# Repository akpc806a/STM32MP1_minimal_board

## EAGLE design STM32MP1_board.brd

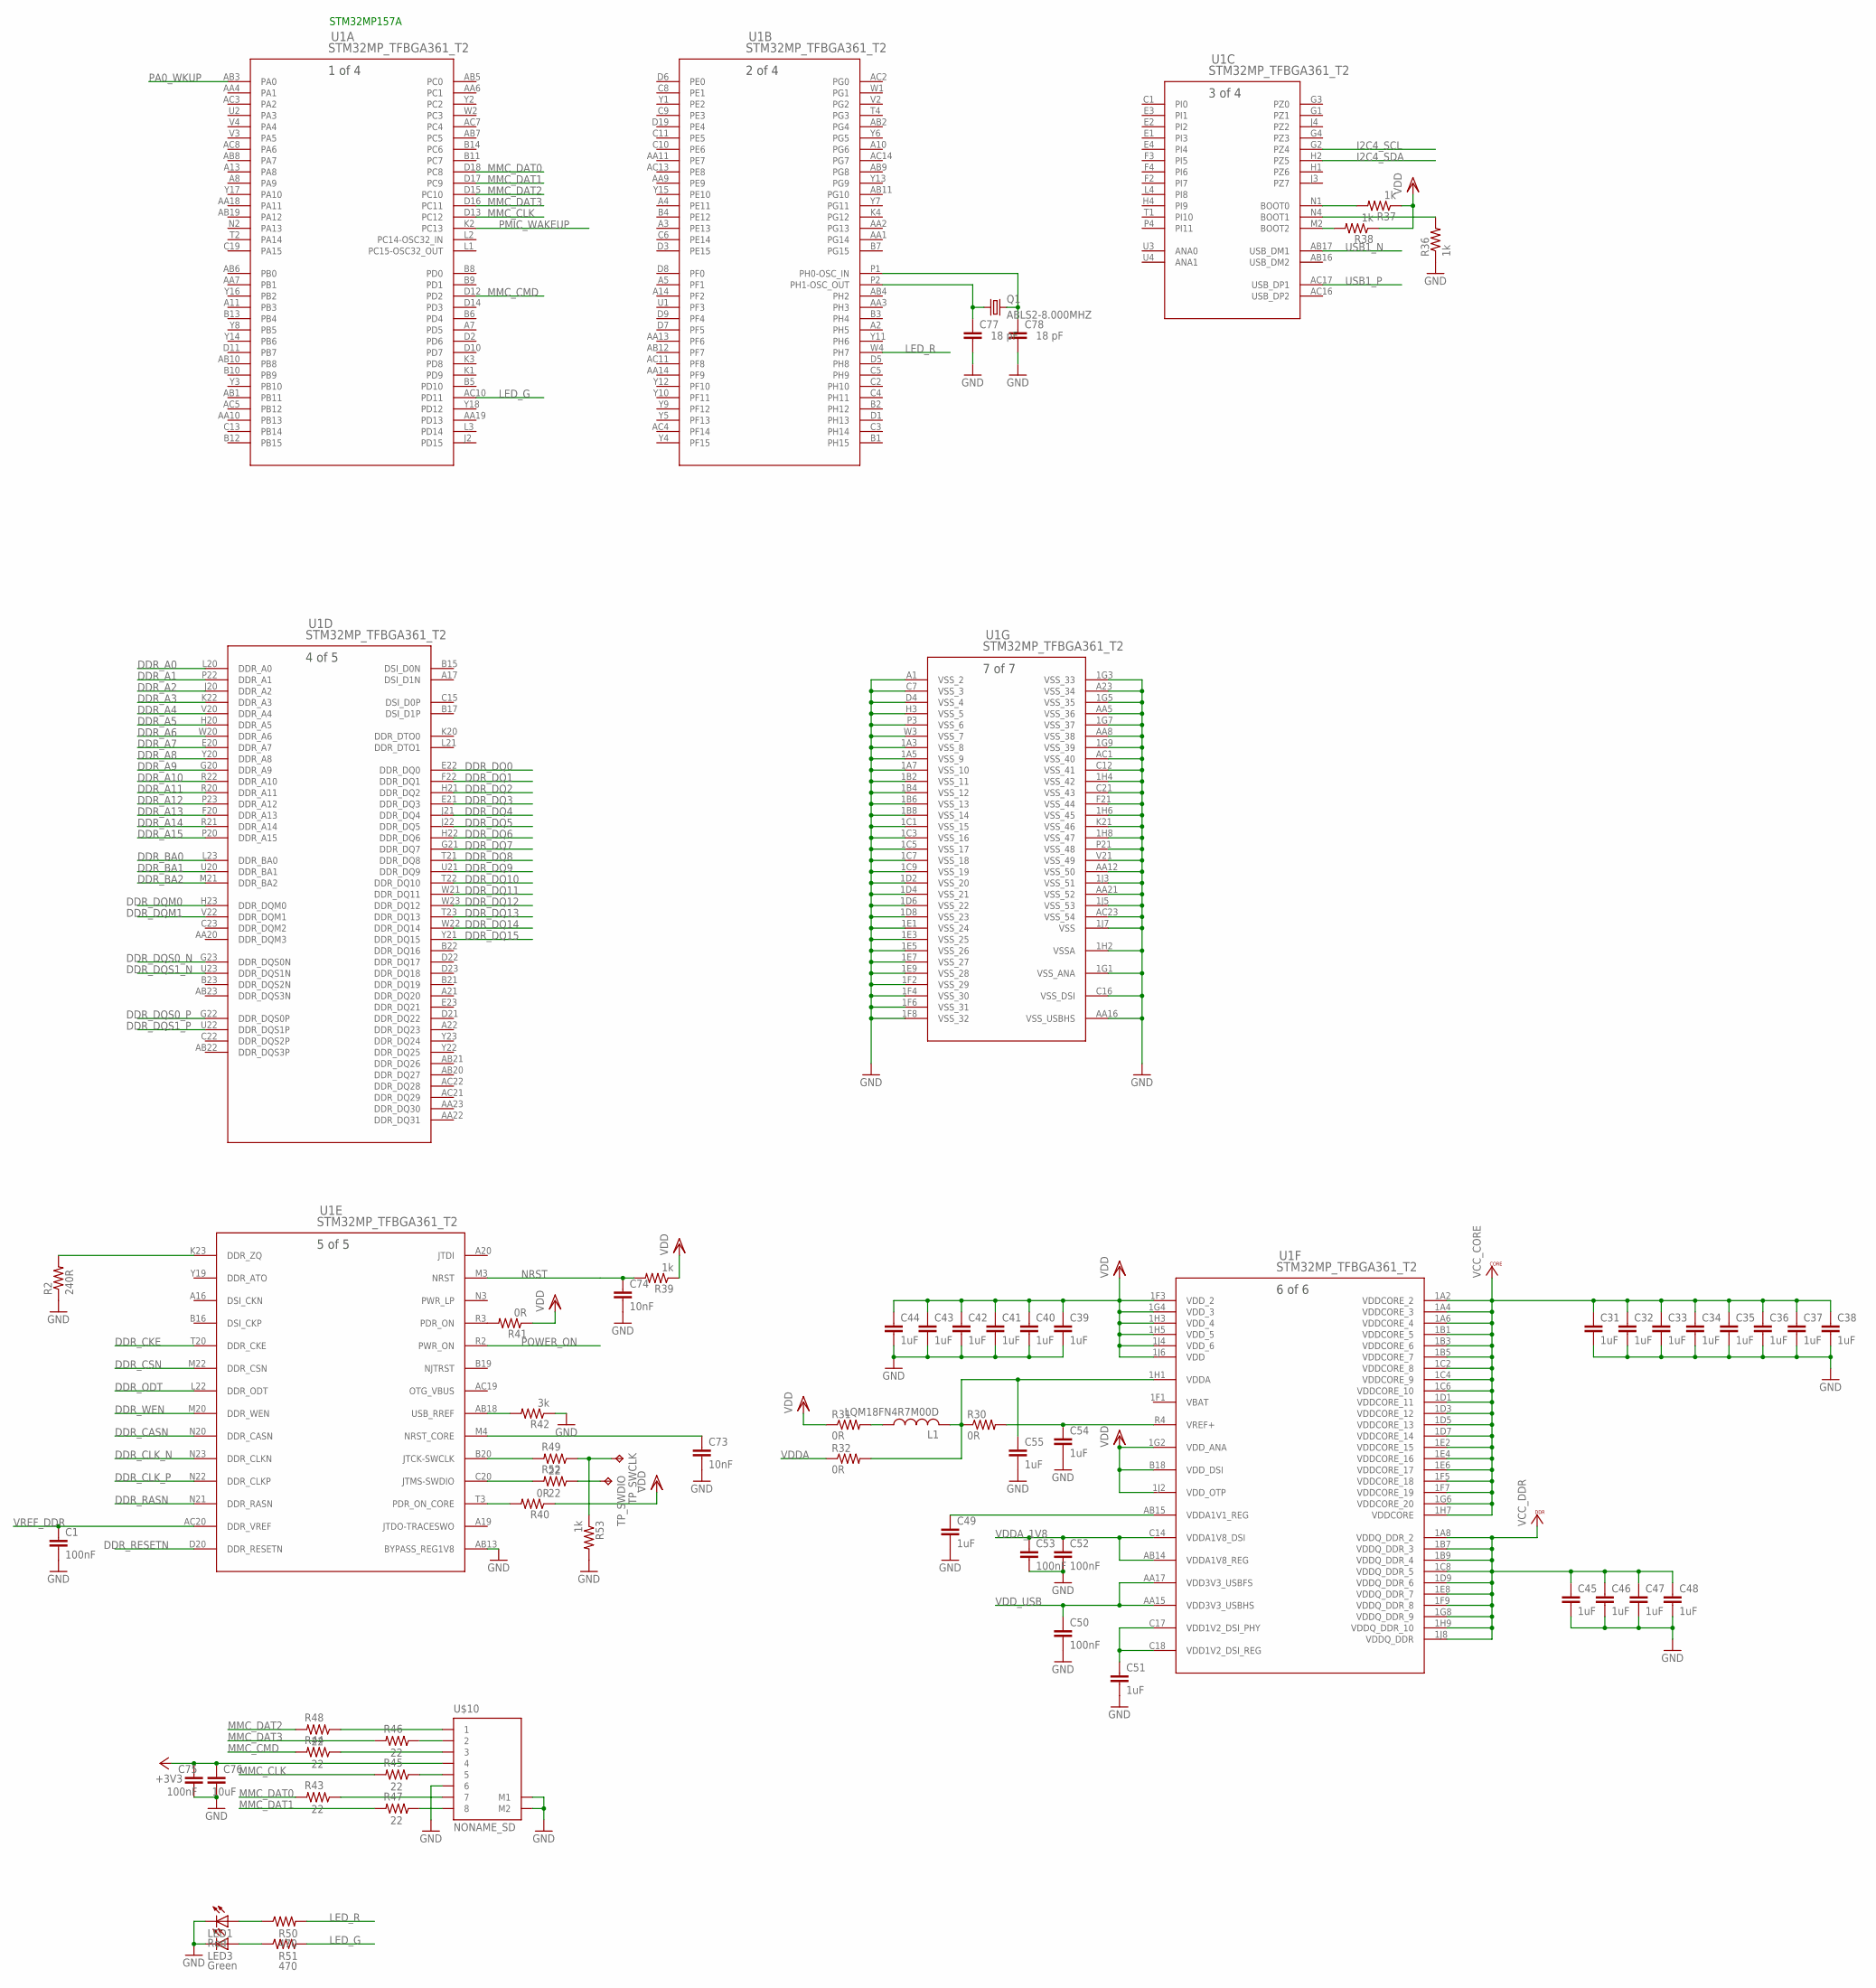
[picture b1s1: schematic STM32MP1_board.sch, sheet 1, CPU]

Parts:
C1, C50, C52, C53, C75: 100nF; C0402K
C31, C32, C33, C34, C35, C36, C37, C38, C39, C40, C41, C42, C43, C44, C45, C46, C47, C48, C49, C51, C54, C55: 1uF; C0402K
C73, C74: 10nF; C0402K
C76: 10uF; C0603K
C77, C78: 18 pF; C0603
L1: LQM18FN4R7M00D; R0603
LED1: Red; LED_SML0603
LED3: Green; LED_SML0603
Q1: ABLS2-8.000MHZ; SM49
R2: 240R; R0402
R30, R31, R32, R40, R41: 0R; R0402
R36, R37, R38, R39, R53: 1k; R0402
R42: 3k; R0402
R43, R44, R45, R46, R47, R48, R49, R52: 22; R0402
R50, R51: 470; R0402
TP_SWCLK: TPTP10SQ; TP10SQ
TP_SWDIO: TPTP10SQ; TP10SQ
U1: STM32MP_TFBGA361_T2; TFBGA361_12X12
U$10: NONAME_SD

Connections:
+3V3: C75.1, C76.1, U$10.4; also elsewhere on the board
DDR_A0: U1.L20 (DDR_A0); also elsewhere on the board
DDR_A1: U1.P22 (DDR_A1); also elsewhere on the board
DDR_A2: U1.J20 (DDR_A2); also elsewhere on the board
DDR_A3: U1.K22 (DDR_A3); also elsewhere on the board
DDR_A4: U1.V20 (DDR_A4); also elsewhere on the board
DDR_A5: U1.H20 (DDR_A5); also elsewhere on the board
DDR_A6: U1.W20 (DDR_A6); also elsewhere on the board
DDR_A7: U1.E20 (DDR_A7); also elsewhere on the board
DDR_A8: U1.Y20 (DDR_A8); also elsewhere on the board
DDR_A9: U1.G20 (DDR_A9); also elsewhere on the board
DDR_A10: U1.R22 (DDR_A10); also elsewhere on the board
DDR_A11: U1.R20 (DDR_A11); also elsewhere on the board
DDR_A12: U1.P23 (DDR_A12); also elsewhere on the board
DDR_A13: U1.F20 (DDR_A13); also elsewhere on the board
DDR_A14: U1.R21 (DDR_A14); also elsewhere on the board
DDR_A15: U1.P20 (DDR_A15)
DDR_BA0: U1.L23 (DDR_BA0); also elsewhere on the board
DDR_BA1: U1.U20 (DDR_BA1); also elsewhere on the board
DDR_BA2: U1.M21 (DDR_BA2); also elsewhere on the board
DDR_CASN: U1.N20 (DDR_CASN); also elsewhere on the board
DDR_CKE: U1.T20 (DDR_CKE); also elsewhere on the board
DDR_CLK_N: U1.N23 (DDR_CLKN); also elsewhere on the board
DDR_CLK_P: U1.N22 (DDR_CLKP); also elsewhere on the board
DDR_CSN: U1.M22 (DDR_CSN); also elsewhere on the board
DDR_DQ0: U1.E22 (DDR_DQ0); also elsewhere on the board
DDR_DQ1: U1.F22 (DDR_DQ1); also elsewhere on the board
DDR_DQ2: U1.H21 (DDR_DQ2); also elsewhere on the board
DDR_DQ3: U1.E21 (DDR_DQ3); also elsewhere on the board
DDR_DQ4: U1.J21 (DDR_DQ4); also elsewhere on the board
DDR_DQ5: U1.J22 (DDR_DQ5); also elsewhere on the board
DDR_DQ6: U1.H22 (DDR_DQ6); also elsewhere on the board
DDR_DQ7: U1.G21 (DDR_DQ7); also elsewhere on the board
DDR_DQ8: U1.T21 (DDR_DQ8); also elsewhere on the board
DDR_DQ9: U1.U21 (DDR_DQ9); also elsewhere on the board
DDR_DQ10: U1.T22 (DDR_DQ10); also elsewhere on the board
DDR_DQ11: U1.W21 (DDR_DQ11); also elsewhere on the board
DDR_DQ12: U1.W23 (DDR_DQ12); also elsewhere on the board
DDR_DQ13: U1.T23 (DDR_DQ13); also elsewhere on the board
DDR_DQ14: U1.W22 (DDR_DQ14); also elsewhere on the board
DDR_DQ15: U1.Y21 (DDR_DQ15); also elsewhere on the board
DDR_DQM0: U1.H23 (DDR_DQM0); also elsewhere on the board
DDR_DQM1: U1.V22 (DDR_DQM1); also elsewhere on the board
DDR_DQS0_N: U1.G23 (DDR_DQS0N); also elsewhere on the board
DDR_DQS0_P: U1.G22 (DDR_DQS0P); also elsewhere on the board
DDR_DQS1_N: U1.U23 (DDR_DQS1N); also elsewhere on the board
DDR_DQS1_P: U1.U22 (DDR_DQS1P); also elsewhere on the board
DDR_ODT: U1.L22 (DDR_ODT); also elsewhere on the board
DDR_RASN: U1.N21 (DDR_RASN); also elsewhere on the board
DDR_RESETN: U1.D20 (DDR_RESETN); also elsewhere on the board
DDR_WEN: U1.M20 (DDR_WEN); also elsewhere on the board
GND: C1.2, C31.2, C32.2, C33.2, C34.2, C35.2, C36.2, C37.2, C38.2, C39.2, C40.2, C41.2, C42.2, C43.2, C44.2, C45.2, C46.2, C47.2, C48.2, C49.2, C50.2, C51.2, C52.2, C53.2, C54.2, C55.2, C73.2, C74.2, C75.2, C76.2, C77.2, C78.2, LED1.C, LED3.C, R2.1, R36.1, R42.1, R53.2, U1.1A3 (VSS_8), U1.1A5 (VSS_9), U1.1A7 (VSS_10), U1.1B2 (VSS_11), U1.1B4 (VSS_12), U1.1B6 (VSS_13), U1.1B8 (VSS_14), U1.1C1 (VSS_15), U1.1C3 (VSS_16), U1.1C5 (VSS_17), U1.1C7 (VSS_18), U1.1C9 (VSS_19), U1.1D2 (VSS_20), U1.1D4 (VSS_21), U1.1D6 (VSS_22), U1.1D8 (VSS_23), U1.1E1 (VSS_24), U1.1E3 (VSS_25), U1.1E5 (VSS_26), U1.1E7 (VSS_27), U1.1E9 (VSS_28), U1.1F2 (VSS_29), U1.1F4 (VSS_30), U1.1F6 (VSS_31), U1.1F8 (VSS_32), U1.1G1 (VSS_ANA), U1.1G3 (VSS_33), U1.1G5 (VSS_35), U1.1G7 (VSS_37), U1.1G9 (VSS_39), U1.1H2 (VSSA), U1.1H4 (VSS_42), U1.1H6 (VSS_45), U1.1H8 (VSS_47), U1.1J3 (VSS_51), U1.1J5 (VSS_53), U1.1J7 (VSS), U1.A1 (VSS_2), U1.A23 (VSS_34), U1.AA5 (VSS_36), U1.AA8 (VSS_38), U1.AA12 (VSS_50), U1.AA16 (VSS_USBHS), U1.AA21 (VSS_52), U1.AB13 (BYPASS_REG1V8), U1.AC1 (VSS_40), U1.AC23 (VSS_54), U1.C7 (VSS_3), U1.C12 (VSS_41), U1.C16 (VSS_DSI), U1.C21 (VSS_43), U1.D4 (VSS_4), U1.F21 (VSS_44), U1.H3 (VSS_5), U1.K21 (VSS_46), U1.P3 (VSS_6), U1.P21 (VSS_48), U1.V21 (VSS_49), U1.W3 (VSS_7), U$10.6, U$10.M1, U$10.M2; also elsewhere on the board
I2C4_SCL: U1.G2 (PZ4); also elsewhere on the board
I2C4_SDA: U1.H2 (PZ5); also elsewhere on the board
LED_G: R51.2, U1.AC10 (PD11)
LED_R: R50.2, U1.W4 (PH7)
MMC_CLK: R45.2, U1.D13 (PC12)
MMC_CMD: R44.2, U1.D12 (PD2)
MMC_DAT0: R43.2, U1.D18 (PC8)
MMC_DAT1: R47.2, U1.D17 (PC9)
MMC_DAT2: R48.2, U1.D15 (PC10)
MMC_DAT3: R46.2, U1.D16 (PC11)
unnamed: R2.2, U1.K23 (DDR_ZQ)
unnamed: C49.1, U1.AB15 (VDDA1V1_REG)
unnamed: C51.1, U1.C17 (VDD1V2_DSI_PHY), U1.C18 (VDD1V2_DSI_REG)
unnamed: C55.1, L1.2, R30.1, R32.2, U1.1H1 (VDDA)
unnamed: C54.1, R30.2, U1.R4 (VREF+)
unnamed: L1.1, R31.2
unnamed: C73.1, U1.M4 (NRST_CORE)
unnamed: R36.2, U1.N4 (BOOT1)
unnamed: R37.2, U1.N1 (BOOT0)
unnamed: R38.2, U1.M2 (BOOT2)
unnamed: C74.1, R39.2
unnamed: R40.2, U1.T3 (PDR_ON_CORE)
unnamed: R41.2, U1.R3 (PDR_ON)
unnamed: R42.2, U1.AB18 (USB_RREF)
unnamed: R49.2, U1.B20 (JTCK-SWCLK)
unnamed: R52.2, U1.C20 (JTMS-SWDIO)
unnamed: R48.1, U$10.1
unnamed: R46.1, U$10.2
unnamed: R44.1, U$10.3
unnamed: R45.1, U$10.5
unnamed: R43.1, U$10.7
unnamed: R47.1, U$10.8
unnamed: R49.1, R53.1, TP_SWCLK.TP
unnamed: R52.1, TP_SWDIO.TP
unnamed: C78.1, Q1.2, U1.P1 (PH0-OSC_IN)
unnamed: C77.1, Q1.1, U1.P2 (PH1-OSC_OUT)
unnamed: LED1.A, R50.1
unnamed: LED3.A, R51.1
NRST: U1.M3 (NRST); also elsewhere on the board
PA0_WKUP: U1.AB3 (PA0); also elsewhere on the board
PMIC_WAKEUP: U1.K2 (PC13); also elsewhere on the board
POWER_ON: U1.R2 (PWR_ON); also elsewhere on the board
USB1_N: U1.AB17 (USB_DM1)
USB1_P: U1.AC17 (USB_DP1)
VBAT: U1.1F1 (VBAT)
VCC_CORE: C31.1, C32.1, C33.1, C34.1, C35.1, C36.1, C37.1, C38.1, U1.1A2 (VDDCORE_2), U1.1A4 (VDDCORE_3), U1.1A6 (VDDCORE_4), U1.1B1 (VDDCORE_5), U1.1B3 (VDDCORE_6), U1.1B5 (VDDCORE_7), U1.1C2 (VDDCORE_8), U1.1C4 (VDDCORE_9), U1.1C6 (VDDCORE_10), U1.1D1 (VDDCORE_11), U1.1D3 (VDDCORE_12), U1.1D5 (VDDCORE_13), U1.1D7 (VDDCORE_14), U1.1E2 (VDDCORE_15), U1.1E4 (VDDCORE_16), U1.1E6 (VDDCORE_17), U1.1F5 (VDDCORE_18), U1.1F7 (VDDCORE_19), U1.1G6 (VDDCORE_20), U1.1H7 (VDDCORE); also elsewhere on the board
VCC_DDR: C45.1, C46.1, C47.1, C48.1, U1.1A8 (VDDQ_DDR_2), U1.1B7 (VDDQ_DDR_3), U1.1B9 (VDDQ_DDR_4), U1.1C8 (VDDQ_DDR_5), U1.1D9 (VDDQ_DDR_6), U1.1E8 (VDDQ_DDR_7), U1.1F9 (VDDQ_DDR_8), U1.1G8 (VDDQ_DDR_9), U1.1H9 (VDDQ_DDR_10), U1.1J8 (VDDQ_DDR); also elsewhere on the board
VDD: C39.1, C40.1, C41.1, C42.1, C43.1, C44.1, R31.1, R37.1, R38.1, R39.1, R40.1, R41.1, U1.1F3 (VDD_2), U1.1G2 (VDD_ANA), U1.1G4 (VDD_3), U1.1H3 (VDD_4), U1.1H5 (VDD_5), U1.1J2 (VDD_OTP), U1.1J4 (VDD_6), U1.1J6 (VDD), U1.B18 (VDD_DSI); also elsewhere on the board
VDDA: R32.1; also elsewhere on the board
VDDA_1V8: C52.1, C53.1, U1.AB14 (VDDA1V8_REG), U1.C14 (VDDA1V8_DSI)
VDD_USB: C50.1, U1.AA15 (VDD3V3_USBHS), U1.AA17 (VDD3V3_USBFS); also elsewhere on the board
VREF_DDR: C1.1, U1.AC20 (DDR_VREF); also elsewhere on the board

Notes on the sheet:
STM32MP157A

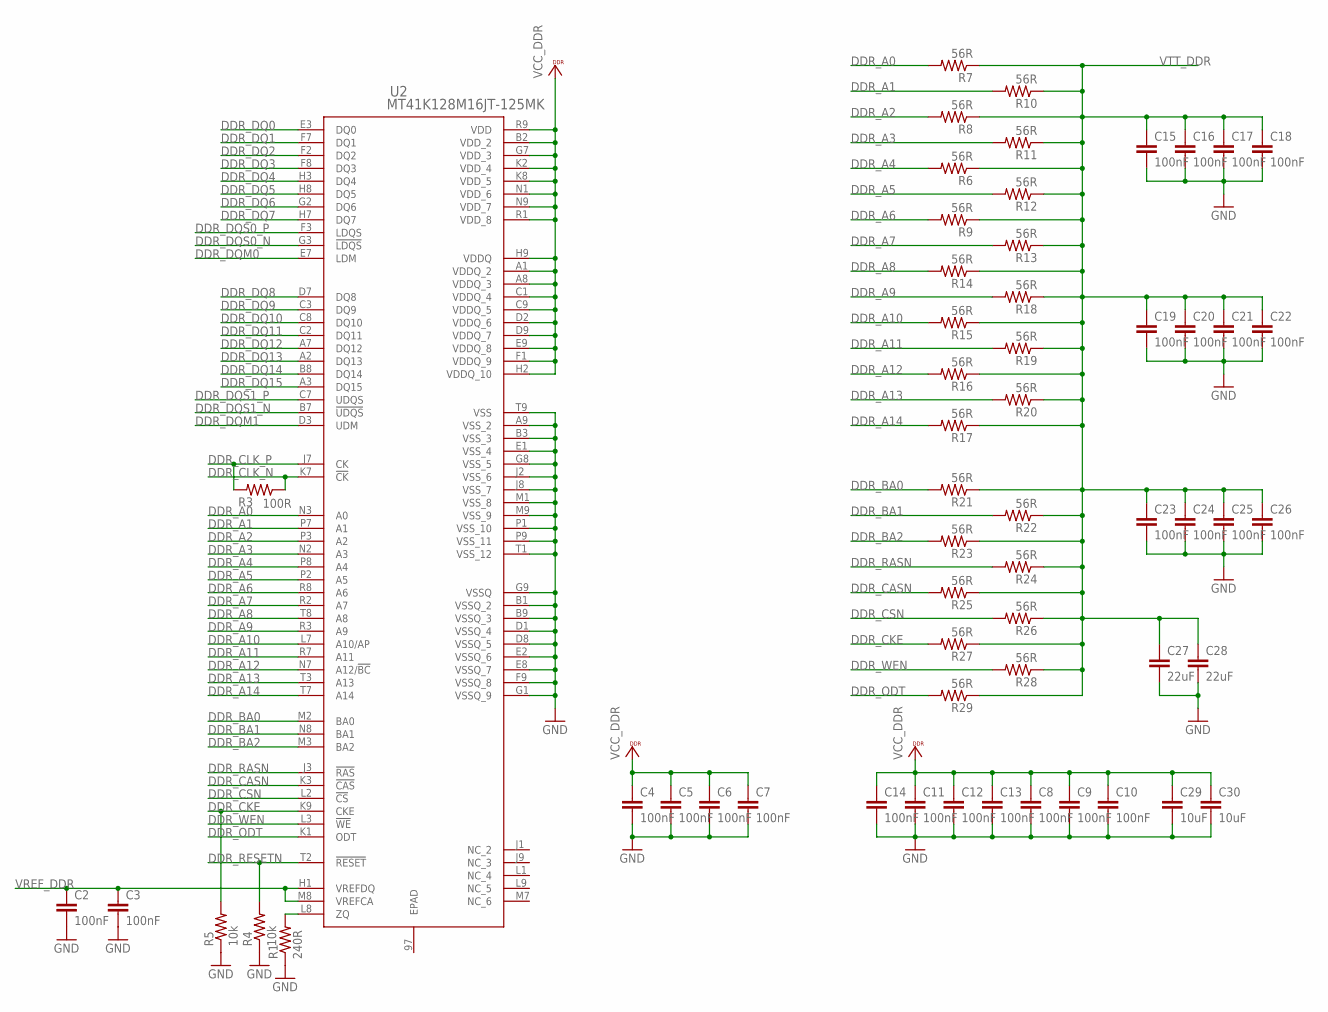
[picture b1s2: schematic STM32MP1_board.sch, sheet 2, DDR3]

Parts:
C2, C3, C4, C5, C6, C7, C8, C9, C10, C11, C12, C13, C14, C15, C16, C17, C18, C19, C20, C21, C22, C23, C24, C25, C26: 100nF; C0402K
C27, C28: 22uF; C0603K
C29, C30: 10uF; C0603K
R1: 240R; R0402
R3: 100R; R0402
R4, R5: 10k; R0402
R6, R7, R8, R9, R10, R11, R12, R13, R14, R15, R16, R17, R18, R19, R20, R21, R22, R23, R24, R25, R26, R27, R28, R29: 56R; R0402
U2: MT41K128M16JT-125MK; FBGA96_8X14

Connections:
DDR_A0: R7.2, U2.N3 (A0); also elsewhere on the board
DDR_A1: R10.2, U2.P7 (A1); also elsewhere on the board
DDR_A2: R8.2, U2.P3 (A2); also elsewhere on the board
DDR_A3: R11.2, U2.N2 (A3); also elsewhere on the board
DDR_A4: R6.2, U2.P8 (A4); also elsewhere on the board
DDR_A5: R12.2, U2.P2 (A5); also elsewhere on the board
DDR_A6: R9.2, U2.R8 (A6); also elsewhere on the board
DDR_A7: R13.2, U2.R2 (A7); also elsewhere on the board
DDR_A8: R14.2, U2.T8 (A8); also elsewhere on the board
DDR_A9: R18.2, U2.R3 (A9); also elsewhere on the board
DDR_A10: R15.2, U2.L7 (A10/AP); also elsewhere on the board
DDR_A11: R19.2, U2.R7 (A11); also elsewhere on the board
DDR_A12: R16.2, U2.N7 (A12/!BC); also elsewhere on the board
DDR_A13: R20.2, U2.T3 (A13); also elsewhere on the board
DDR_A14: R17.2, U2.T7 (A14); also elsewhere on the board
DDR_BA0: R21.2; also elsewhere on the board
DDR_BA1: R22.2; also elsewhere on the board
DDR_BA2: R23.2; also elsewhere on the board
DDR_CASN: R25.2, U2.K3 (!CAS); also elsewhere on the board
DDR_CKE: R5.2, R27.2, U2.K9 (CKE); also elsewhere on the board
DDR_CLK_N: R3.1, U2.K7 (!CK); also elsewhere on the board
DDR_CLK_P: R3.2, U2.J7 (CK); also elsewhere on the board
DDR_CSN: R26.2, U2.L2 (!CS); also elsewhere on the board
DDR_DQ0: U2.E3 (DQ0); also elsewhere on the board
DDR_DQ1: U2.F7 (DQ1); also elsewhere on the board
DDR_DQ2: U2.F2 (DQ2); also elsewhere on the board
DDR_DQ3: U2.F8 (DQ3); also elsewhere on the board
DDR_DQ4: U2.H3 (DQ4); also elsewhere on the board
DDR_DQ5: U2.H8 (DQ5); also elsewhere on the board
DDR_DQ6: U2.G2 (DQ6); also elsewhere on the board
DDR_DQ7: U2.H7 (DQ7); also elsewhere on the board
DDR_DQ8: U2.D7 (DQ8); also elsewhere on the board
DDR_DQ9: U2.C3 (DQ9); also elsewhere on the board
DDR_DQ10: U2.C8 (DQ10); also elsewhere on the board
DDR_DQ11: U2.C2 (DQ11); also elsewhere on the board
DDR_DQ12: U2.A7 (DQ12); also elsewhere on the board
DDR_DQ13: U2.A2 (DQ13); also elsewhere on the board
DDR_DQ14: U2.B8 (DQ14); also elsewhere on the board
DDR_DQ15: U2.A3 (DQ15); also elsewhere on the board
DDR_DQM0: U2.E7 (LDM); also elsewhere on the board
DDR_DQM1: U2.D3 (UDM); also elsewhere on the board
DDR_DQS0_N: U2.G3 (!LDQS); also elsewhere on the board
DDR_DQS0_P: U2.F3 (LDQS); also elsewhere on the board
DDR_DQS1_N: U2.B7 (!UDQS); also elsewhere on the board
DDR_DQS1_P: U2.C7 (UDQS); also elsewhere on the board
DDR_ODT: R29.2, U2.K1 (ODT); also elsewhere on the board
DDR_RASN: R24.2, U2.J3 (!RAS); also elsewhere on the board
DDR_RESETN: R4.2, U2.T2 (!RESET); also elsewhere on the board
DDR_WEN: R28.2, U2.L3 (!WE); also elsewhere on the board
GND: C2.2, C3.2, C4.2, C5.2, C6.2, C7.2, C8.2, C9.2, C10.2, C11.2, C12.2, C13.2, C14.2, C15.2, C16.2, C17.2, C18.2, C19.2, C20.2, C21.2, C22.2, C23.2, C24.2, C25.2, C26.2, C27.2, C28.2, C29.2, C30.2, R1.1, R4.1, R5.1, U2.A9 (VSS_2), U2.B1 (VSSQ_2), U2.B3 (VSS_3), U2.B9 (VSSQ_3), U2.D1 (VSSQ_4), U2.D8 (VSSQ_5), U2.E1 (VSS_4), U2.E2 (VSSQ_6), U2.E8 (VSSQ_7), U2.F9 (VSSQ_8), U2.G1 (VSSQ_9), U2.G8 (VSS_5), U2.G9 (VSSQ), U2.J2 (VSS_6), U2.J8 (VSS_7), U2.M1 (VSS_8), U2.M9 (VSS_9), U2.P1 (VSS_10), U2.P9 (VSS_11), U2.T1 (VSS_12), U2.T9 (VSS); also elsewhere on the board
unnamed: R1.2, U2.L8 (ZQ)
VCC_DDR: C4.1, C5.1, C6.1, C7.1, C8.1, C9.1, C10.1, C11.1, C12.1, C13.1, C14.1, C29.1, C30.1, U2.A1 (VDDQ_2), U2.A8 (VDDQ_3), U2.B2 (VDD_2), U2.C1 (VDDQ_4), U2.C9 (VDDQ_5), U2.D2 (VDDQ_6), U2.D9 (VDDQ_7), U2.E9 (VDDQ_8), U2.F1 (VDDQ_9), U2.G7 (VDD_3), U2.H2 (VDDQ_10), U2.H9 (VDDQ), U2.K2 (VDD_4), U2.K8 (VDD_5), U2.N1 (VDD_6), U2.N9 (VDD_7), U2.R1 (VDD_8), U2.R9 (VDD); also elsewhere on the board
VREFDQ: U2.H1 (VREFDQ)
VREF_DDR: C2.1, C3.1, U2.M8 (VREFCA); also elsewhere on the board
VTT_DDR: C15.1, C16.1, C17.1, C18.1, C19.1, C20.1, C21.1, C22.1, C23.1, C24.1, C25.1, C26.1, C27.1, C28.1, R6.1, R7.1, R8.1, R9.1, R10.1, R11.1, R12.1, R13.1, R14.1, R15.1, R16.1, R17.1, R18.1, R19.1, R20.1, R21.1, R22.1, R23.1, R24.1, R25.1, R26.1, R27.1, R28.1, R29.1; also elsewhere on the board

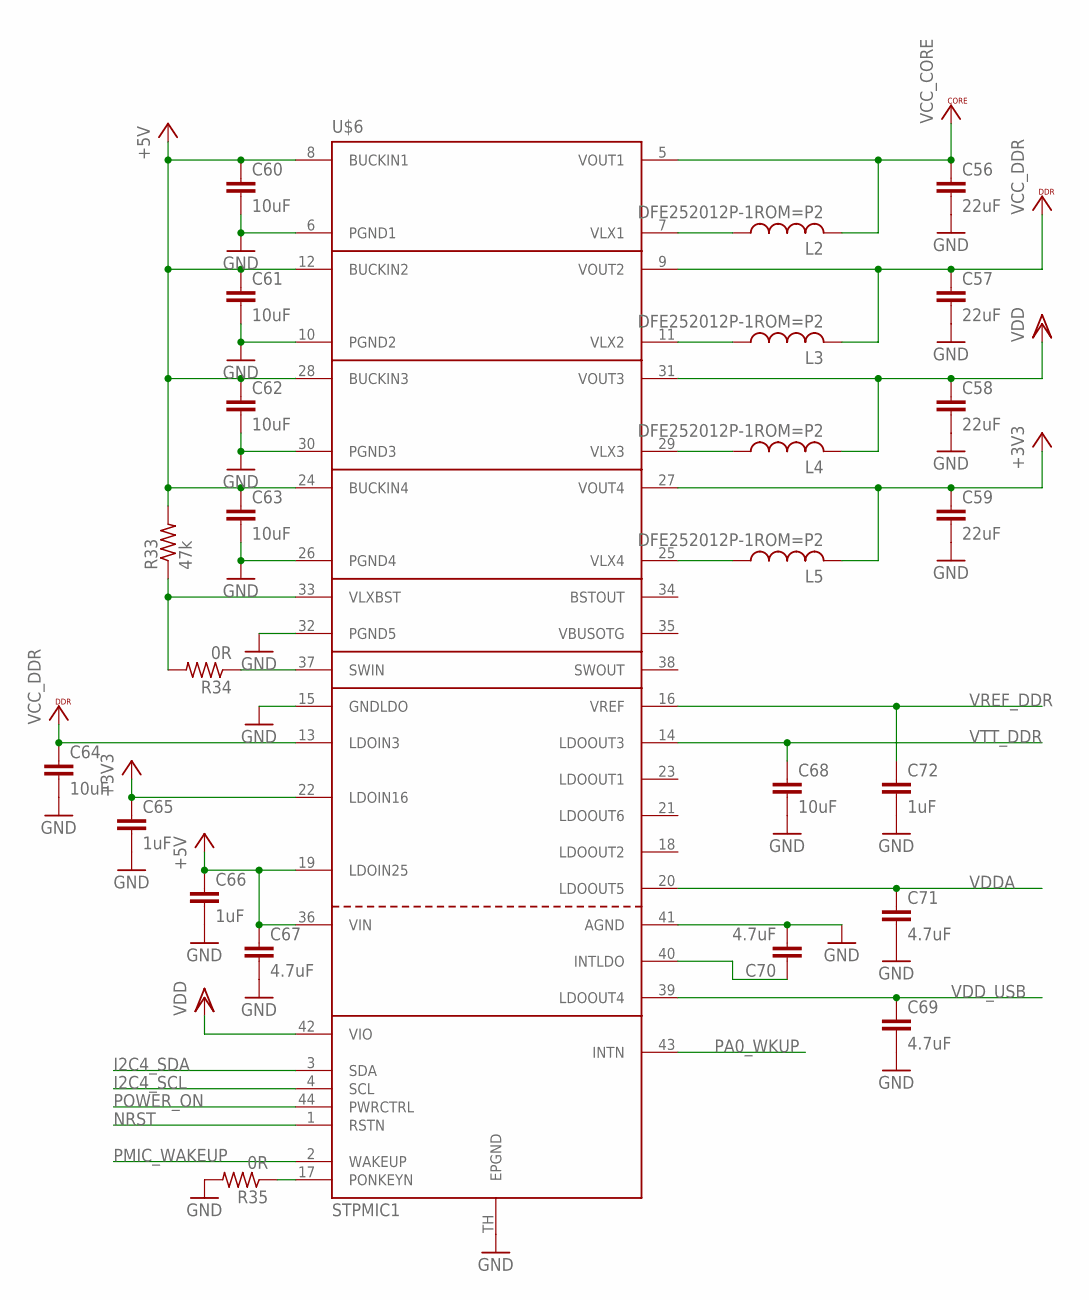
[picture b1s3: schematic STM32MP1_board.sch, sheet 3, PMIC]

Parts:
C56, C57, C58, C59: 22uF; C0603K
C60, C61, C62, C63, C64, C68: 10uF; C0603K
C65, C66, C72: 1uF; C0402K
C67, C69, C70, C71: 4.7uF; C0402K
L2, L3, L4, L5: DFE252012P-1ROM=P2; L2825P
R33: 47k; R0402
R34, R35: 0R; R0402
U$6: STPMIC1; MLF44-TH

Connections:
+3V3: C59.1, C65.1, L5.2, U$6.22 (LDOIN16), U$6.27 (VOUT4); also elsewhere on the board
+5V: C60.1, C61.1, C62.1, C63.1, C66.1, C67.1, R33.2, U$6.8 (BUCKIN1), U$6.12 (BUCKIN2), U$6.19 (LDOIN25), U$6.24 (BUCKIN4), U$6.28 (BUCKIN3), U$6.36 (VIN)
GND: C56.2, C57.2, C58.2, C59.2, C60.2, C61.2, C62.2, C63.2, C64.2, C65.2, C66.2, C67.2, C68.2, C69.2, C70.2, C71.2, C72.2, R35.2, U$6.6 (PGND1), U$6.10 (PGND2), U$6.15 (GNDLDO), U$6.26 (PGND4), U$6.30 (PGND3), U$6.32 (PGND5), U$6.41 (AGND), U$6.TH (EPGND); also elsewhere on the board
I2C4_SCL: U$6.4 (SCL); also elsewhere on the board
I2C4_SDA: U$6.3 (SDA); also elsewhere on the board
unnamed: L2.1, U$6.7 (VLX1)
unnamed: L3.1, U$6.11 (VLX2)
unnamed: L4.1, U$6.29 (VLX3)
unnamed: L5.1, U$6.25 (VLX4)
unnamed: R33.1, R34.2, U$6.33 (VLXBST)
unnamed: R34.1, U$6.37 (SWIN)
unnamed: R35.1, U$6.17 (PONKEYN)
unnamed: C70.1, U$6.40 (INTLDO)
NRST: U$6.1 (RSTN); also elsewhere on the board
PA0_WKUP: U$6.43 (INTN); also elsewhere on the board
PMIC_WAKEUP: U$6.2 (WAKEUP); also elsewhere on the board
POWER_ON: U$6.44 (PWRCTRL); also elsewhere on the board
VCC_CORE: C56.1, L2.2, U$6.5 (VOUT1); also elsewhere on the board
VCC_DDR: C57.1, C64.1, L3.2, U$6.9 (VOUT2), U$6.13 (LDOIN3); also elsewhere on the board
VDD: C58.1, L4.2, U$6.31 (VOUT3), U$6.42 (VIO); also elsewhere on the board
VDDA: C71.1, U$6.20 (LDOOUT5); also elsewhere on the board
VDD_USB: C69.1, U$6.39 (LDOOUT4); also elsewhere on the board
VREF_DDR: C72.1, U$6.16 (VREF); also elsewhere on the board
VTT_DDR: C68.1, U$6.14 (LDOOUT3); also elsewhere on the board

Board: 2 copper layers, 145 parts (0 on the bottom side), 111 nets, no tracks yet.

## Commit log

2019-03-30 initial commit (first draft of the circuit)
